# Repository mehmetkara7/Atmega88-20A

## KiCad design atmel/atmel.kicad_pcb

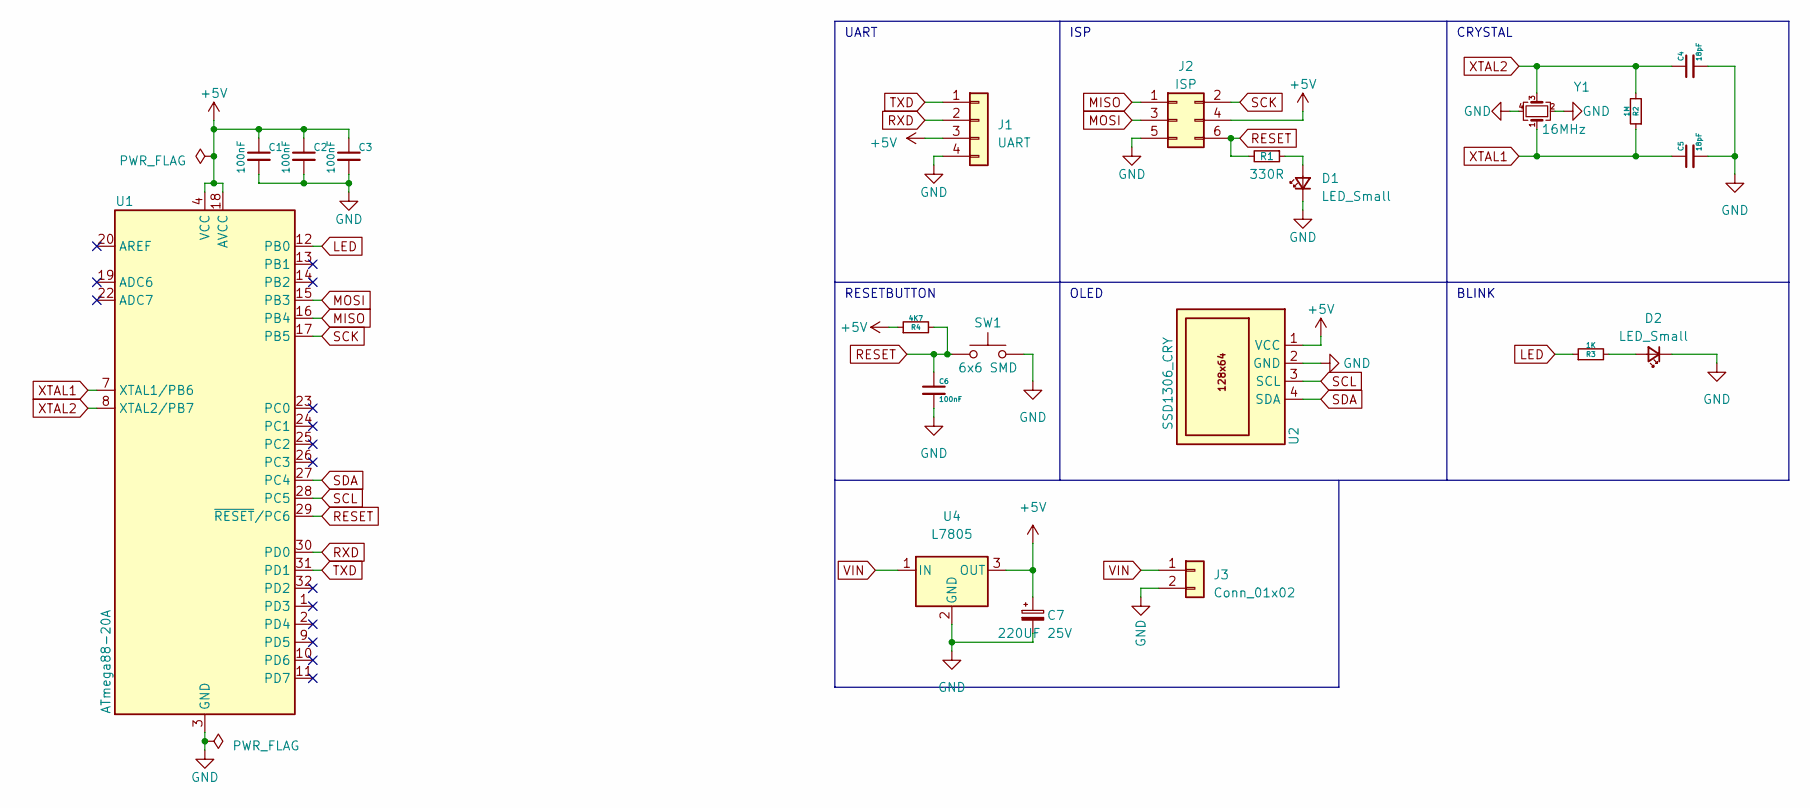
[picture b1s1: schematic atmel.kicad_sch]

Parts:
C1, C2, C3, C6: 100nF; C_0805_2012Metric
C4, C5: 18pF; C_0603_1608Metric
C7: 220UF 25V; CP_Elec_8x10.5
D1, D2: LED_Small; LED_0805_2012Metric
J1: UART; PinHeader_1x04_P2.54mm_Vertical
J2: ISP; PinHeader_2x03_P2.54mm_Vertical
J3: Conn_01x02; TerminalBlock_Phoenix_MKDS-1,5-2-5.08_1x02_P5.08mm_Horizont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
R1: 330R; R_0805_2012Metric
R2: 1M; R_0805_2012Metric
R3: 1K; R_0805_2012Metric
R4: 4K7; R_0805_2012Metric
SW1: 6x6 SMD; SW_SPST_CK_RS282G05A3
U1: ATmega88-20A; TQFP-32_7x7mm_P0.8mm
U2: SSD1306_CRY; 128x64OLED
U4: L7805; TO-252-2
Y1: 16MHz; Crystal_SMD_5032-4Pin_5.0x3.2mm

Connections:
+5V: C1.1, C2.1, C3.1, C7.1, J1.3, J2.4, R4.1, U1.4 (VCC), U1.6 (VCC), U1.18 (AVCC), U2.1 (VCC), U4.3 (OUT)
GND: C1.2, C2.2, C3.2, C4.2, C5.2, C6.2, C7.2, D1.1 (K), D2.1 (K), J1.4, J2.5, J3.2, SW1.2, U1.3 (GND), U1.5 (GND), U1.21 (GND), U2.2 (GND), U4.2 (GND), Y1.2, Y1.4
LED: R3.1, U1.12 (PB0)
MISO: J2.1, U1.16 (PB4)
MOSI: J2.3, U1.15 (PB3)
unnamed: D1.2 (A), R1.1
unnamed: D2.2 (A), R3.2
RESET: C6.1, J2.6, R1.2, R4.2, SW1.1, U1.29 (~RESET/PC6)
RXD: J1.2, U1.30 (PD0)
SCK: J2.2, U1.17 (PB5)
SCL: U1.28 (PC5), U2.3 (SCL)
SDA: U1.27 (PC4), U2.4 (SDA)
TXD: J1.1, U1.31 (PD1)
VIN: J3.1, U4.1 (IN)
XTAL1: C5.1, R2.1, U1.7 (XTAL1/PB6), Y1.1
XTAL2: C4.1, R2.2, U1.8 (XTAL2/PB7), Y1.3

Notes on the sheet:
OLED
RESETBUTTON
BLINK
UART
ISP
CRYSTAL

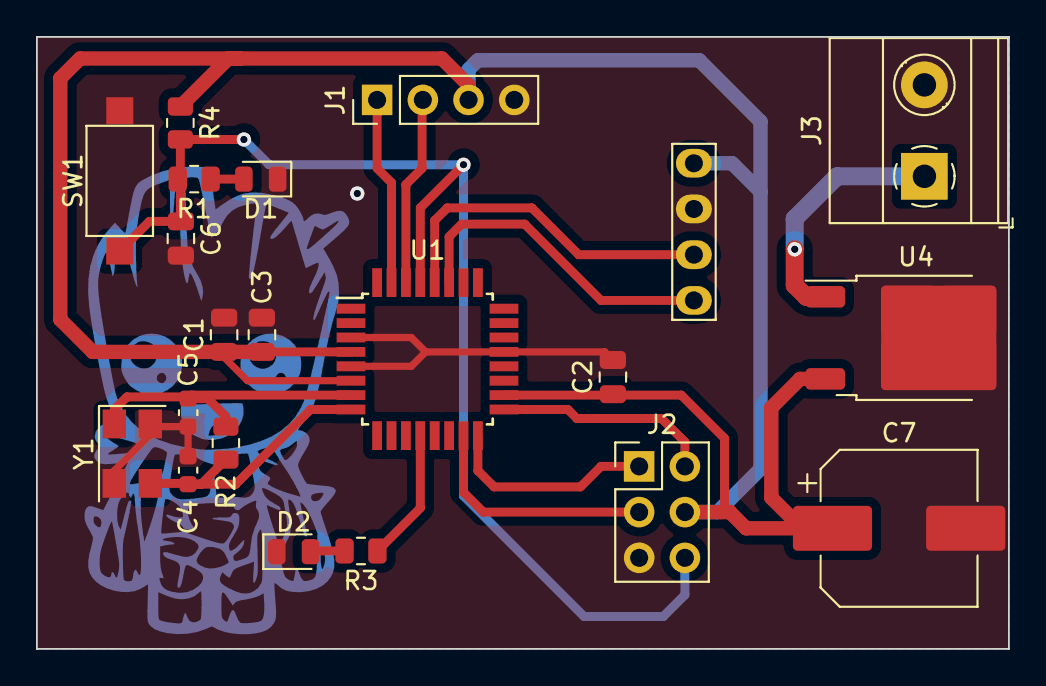
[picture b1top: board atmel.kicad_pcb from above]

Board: 2 copper layers, 54.0 x 34.0 mm, 21 parts (0 on the bottom side), 16 nets.
